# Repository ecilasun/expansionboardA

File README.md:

# expansionboardA

This repository contains KiCAD 7 project files for an expansion module built for QMTECH A7 200T core board.
Required libraries (models and symbols) are included with the project.

# Bill of materials

See expansionboardA.cv file for the list of components required for a fully populated board. Please note that some are optional (such as the USB controller chips) depending on your application.

# Default SoC, ROM image and samples

For hardware, visit https://github.com/ecilasun/tinysys. The project files require a recent version of Vivado suite to work.

For software, visit https://github.com/ecilasun/riscvtool and check the tinysys directory for the default ROM image and samples. The ROM image comes in two parts: the actual executable ROM and another one (fetch) that contains instruction sequences to inject on hardware/software interrupts. Samples demonstrate majority of the capabilities of the tinysys SoC itself.

# Device manual:
- Populating the board
    - USB-C power
    - Debug port
    - SD Card reader
    - HDMI port
    - A/D converter
    - USB-C client
    - USB-A host
    - Board carrier headers
    - Fan connection
    - Audio
    - QMTECH A7-200T core board
- Installing tinysys SoC bitware
- Compiling and running demo software on the board
    - Compiler toolchain installation
    - Hello, board!
- Operating system how-tos
    - List of syscalls
    - Memory layout
    - Operating principles
    - Debugging
- Device manuals:
    - Raw audio
    - OPL2 audio
    - GPU
    - DMA
    - A/D converter
    - Interrupt handling
    - Task system

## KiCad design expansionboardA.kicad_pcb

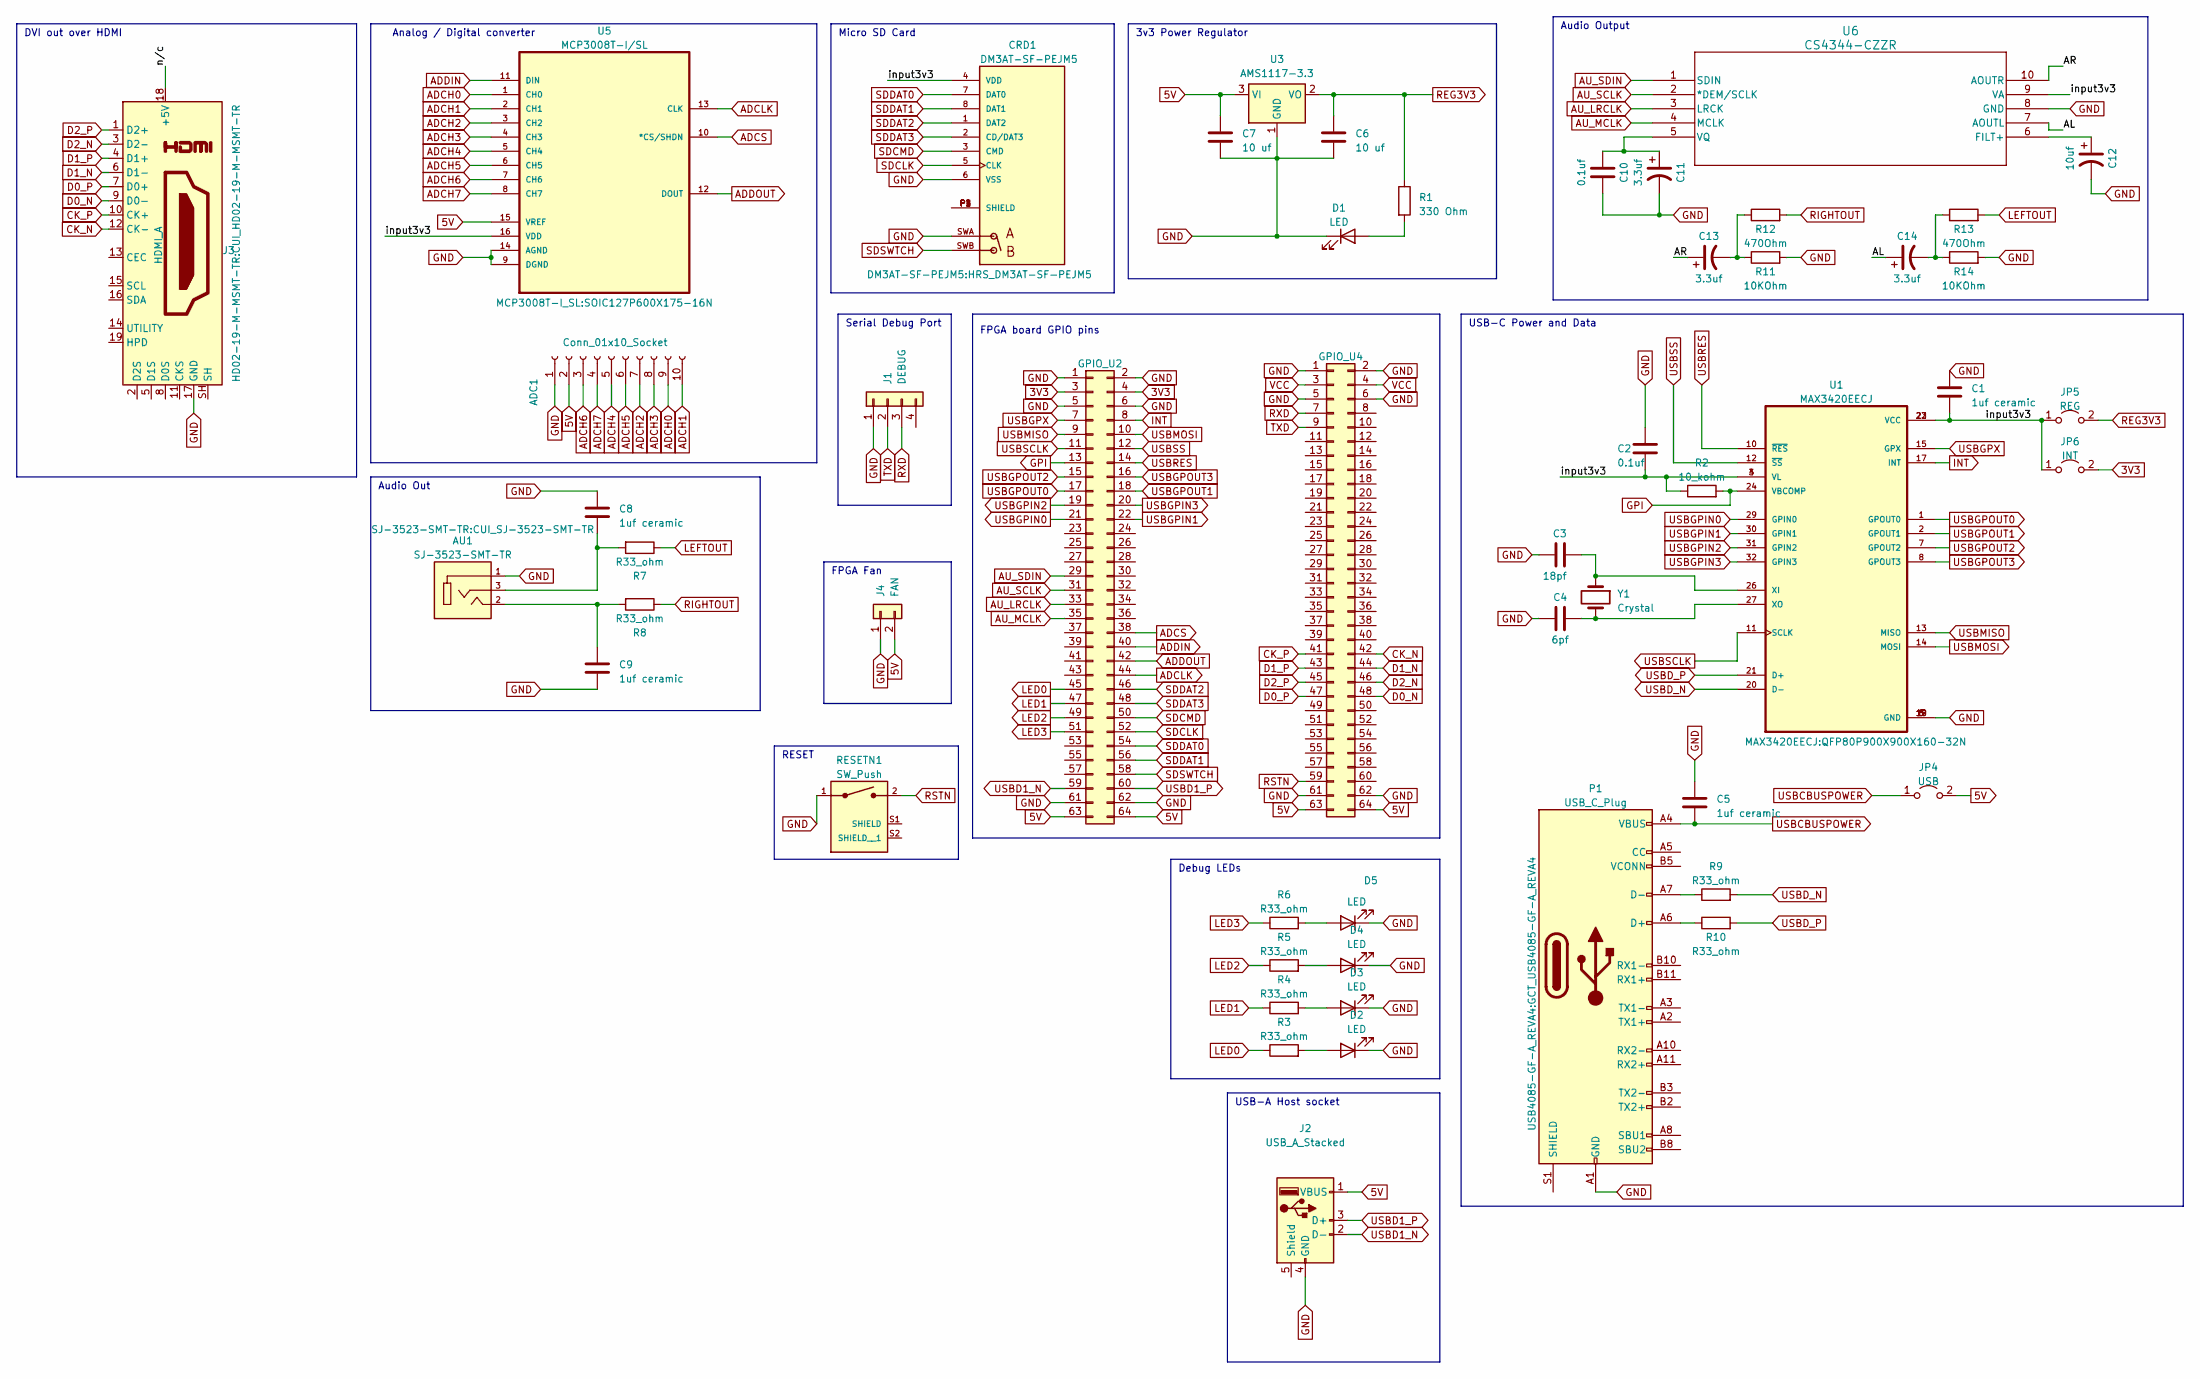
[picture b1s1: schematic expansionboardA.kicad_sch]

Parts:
ADC1: Conn_01x10_Socket; PinSocket_2x05_P2.54mm_Horizontal
AU1: SJ-3523-SMT-TR; CUI_SJ-3523-SMT-TR
C1, C5, C8, C9: 1uf ceramic; C_0603_1608Metric_Pad1.08x0.95mm_HandSolder
C2, C10: 0.1uf; C_0603_1608Metric_Pad1.08x0.95mm_HandSolder
C3: 18pf; C_0603_1608Metric_Pad1.08x0.95mm_HandSolder
C4: 6pf; C_0603_1608Metric_Pad1.08x0.95mm_HandSolder
C6, C7: 10 uf; C_0805_2012Metric_Pad1.18x1.45mm_HandSolder
C11, C13, C14: 3.3uf; CP_Radial_D10.0mm_P5.00mm
C12: 10uf; CP_Elec_6.3x5.9
CRD1: DM3AT-SF-PEJM5; HRS_DM3AT-SF-PEJM5
D1, D2, D3, D4, D5: LED; LED_1206_3216Metric_Pad1.42x1.75mm_HandSolder
J1: DEBUG; PinSocket_1x04_P2.54mm_Horizontal
J2: USB_A_Stacked; USB_A_Molex_67643_Horizontal
J3: HDMI_A; CUI_HD02-19-M-MSMT-TR
J4: FAN; PinHeader_1x02_P2.54mm_Vertical
JP4: USB; SolderJumper-2_P1.3mm_Open_Pad1.0x1.5mm
JP5: REG; SolderJumper-2_P1.3mm_Open_Pad1.0x1.5mm
JP6: INT; SolderJumper-2_P1.3mm_Open_Pad1.0x1.5mm
P1: USB_C_Plug; GCT_USB4085-GF-A_REVA4
R1: 330 Ohm; R_0603_1608Metric_Pad0.98x0.95mm_HandSolder
R2: 10_kohm; R_0603_1608Metric_Pad0.98x0.95mm_HandSolder
R3, R4, R5, R6, R7, R8, R9, R10: R33_ohm; R_0603_1608Metric_Pad0.98x0.95mm_HandSolder
R11, R14: 10KOhm; R_Axial_DIN0207_L6.3mm_D2.5mm_P7.62mm_Horizontal
R12, R13: 470Ohm; R_Axial_DIN0204_L3.6mm_D1.6mm_P5.08mm_Horizontal
RESETN1: SW_Push; SW_1-1825027-1; PARTREV G4
U1: MAX3420EECJ; QFP80P900X900X160-32N
U2: GPIO_U2; PinSocket_2x32_P2.54mm_Vertical
U3: AMS1117-3.3; SOT-89-3_Handsoldering
U4: GPIO_U4; PinSocket_2x32_P2.54mm_Vertical
U5: MCP3008T-I/SL; SOIC127P600X175-16N; MPN MCP3008T-I/SL
U6: CS4344-CZZR; CIR_3TSSOP-10
Y1: Crystal; Crystal_AT310_D3.0mm_L10.0mm_Horizontal

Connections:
3V3: JP6.2 (B), U2.3, U2.4
5V: ADC1.2, C7.1, J2.1 (VBUS), J4.2, JP4.2 (B), U2.63, U2.64, U3.3 (VI), U4.63, U4.64, U5.15 (VREF)
/AL: C14.1, U6.7 (AOUTL)
/AR: C13.1, U6.10 (AOUTR)
/input3v3: C1.2, C2.2, CRD1.4 (VDD), JP5.1 (A), JP6.1 (A), R2.1, U1.3 (VL), U1.4 (VL), U1.22 (VCC), U1.23 (VCC), U5.16 (VDD), U6.9 (VA)
/n/c: J3.18 (+5V)
ADCH0: ADC1.9, U5.1 (CH0)
ADCH1: ADC1.10, U5.2 (CH1)
ADCH2: ADC1.7, U5.3 (CH2)
ADCH3: ADC1.8, U5.4 (CH3)
ADCH4: ADC1.5, U5.5 (CH4)
ADCH5: ADC1.6, U5.6 (CH5)
ADCH6: ADC1.3, U5.7 (CH6)
ADCH7: ADC1.4, U5.8 (CH7)
ADCLK: U2.44, U5.13 (CLK)
ADCS: U2.38, U5.10 (*CS/SHDN)
ADDIN: U2.40, U5.11 (DIN)
ADDOUT: U2.42, U5.12 (DOUT)
AU_LRCLK: U2.33, U6.3 (LRCK)
AU_MCLK: U2.35, U6.4 (MCLK)
AU_SCLK: U2.31, U6.2 (*DEM/SCLK)
AU_SDIN: U2.29, U6.1 (SDIN)
CK_N: J3.12 (CK-), U4.42
CK_P: J3.10 (CK+), U4.41
D0_N: J3.9 (D0-), U4.48
D0_P: J3.7 (D0+), U4.47
D1_N: J3.6 (D1-), U4.44
D1_P: J3.4 (D1+), U4.43
D2_N: J3.3 (D2-), U4.46
D2_P: J3.1 (D2+), U4.45
GND: ADC1.1, AU1.1, C1.1, C2.1, C3.1, C4.1, C5.1, C6.2, C7.2, C8.1, C9.2, C10.2, C11.2, C12.2, CRD1.6 (VSS), CRD1.SWA, D1.1 (K), D2.1 (K), D3.1 (K), D4.1 (K), D5.1 (K), J1.1, J2.4 (GND), J3.17 (GND), J4.1, P1.A1 (GND), P1.A12 (GND), P1.B1 (GND), P1.B12 (GND), R11.2, R14.2, RESETN1.1, U1.5 (GND), U1.6 (GND), U1.18 (GND), U1.19 (GND), U2.1, U2.2, U2.5, U2.6, U2.61, U2.62, U3.1 (GND), U4.1, U4.2, U4.5, U4.6, U4.61, U4.62, U5.9 (DGND), U5.14 (AGND), U6.8 (GND)
GPI: R2.2, U1.24 (VBCOMP), U2.13
INT: U1.17 (INT), U2.8
LED0: R3.1, U2.45
LED1: R4.1, U2.47
LED2: R5.1, U2.49
LED3: R6.1, U2.51
LEFTOUT: R7.1, R13.2
unnamed: AU1.2, C9.1, R8.2
unnamed: AU1.3, C8.2, R7.2
unnamed: C13.2, R11.1, R12.1
unnamed: C14.2, R13.1, R14.1
unnamed: CRD1.P1 (SHIELD), CRD1.P2 (SHIELD), CRD1.P3 (SHIELD), CRD1.P4 (SHIELD)
unnamed: D1.2 (A), R1.2
unnamed: D2.2 (A), R3.2
unnamed: D3.2 (A), R4.2
unnamed: D4.2 (A), R5.2
unnamed: D5.2 (A), R6.2
unnamed: P1.A6 (D+), R10.1
unnamed: P1.A7 (D-), R9.1
unnamed: C3.2, U1.26 (XI), Y1.1
unnamed: C4.2, U1.27 (XO), Y1.2
unnamed: C12.1, U6.6 (FILT+)
unnamed: C10.1, C11.1, U6.5 (VQ)
REG3V3: C6.1, JP5.2 (B), R1.1, U3.2 (VO)
RIGHTOUT: R8.1, R12.2
RSTN: RESETN1.2, U4.59
RXD: J1.3, U4.7
SDCLK: CRD1.5 (CLK), U2.52
SDCMD: CRD1.3 (CMD), U2.50
SDDAT0: CRD1.7 (DAT0), U2.54
SDDAT1: CRD1.8 (DAT1), U2.56
SDDAT2: CRD1.1 (DAT2), U2.46
SDDAT3: CRD1.2 (CD/DAT3), U2.48
SDSWTCH: CRD1.SWB, U2.58
TXD: J1.2, U4.9
USBCBUSPOWER: C5.2, JP4.1 (A), P1.A4 (VBUS), P1.A9 (VBUS), P1.B4 (VBUS), P1.B9 (VBUS)
USBD1_N: J2.2 (D-), U2.59
USBD1_P: J2.3 (D+), U2.60
USBD_N: R9.2, U1.20 (D-)
USBD_P: R10.2, U1.21 (D+)
USBGPIN0: U1.29 (GPIN0), U2.21
USBGPIN1: U1.30 (GPIN1), U2.22
USBGPIN2: U1.31 (GPIN2), U2.19
USBGPIN3: U1.32 (GPIN3), U2.20
USBGPOUT0: U1.1 (GPOUT0), U2.17
USBGPOUT1: U1.2 (GPOUT1), U2.18
USBGPOUT2: U1.7 (GPOUT2), U2.15
USBGPOUT3: U1.8 (GPOUT3), U2.16
USBGPX: U1.15 (GPX), U2.7
USBMISO: U1.13 (MISO), U2.9
USBMOSI: U1.14 (MOSI), U2.10
USBRES: U1.10 (~RES), U2.14
USBSCLK: U1.11 (SCLK), U2.11
USBSS: U1.12 (~SS), U2.12
VCC: U4.3, U4.4

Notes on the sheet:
Serial Debug Port
Audio Output
USB-A Host socket
FPGA board GPIO pins
Micro SD Card
USB-C Power and Data
Debug LEDs
Audio Out
RESET
3v3 Power Regulator
DVI out over HDMI
FPGA Fan
Analog / Digital converter

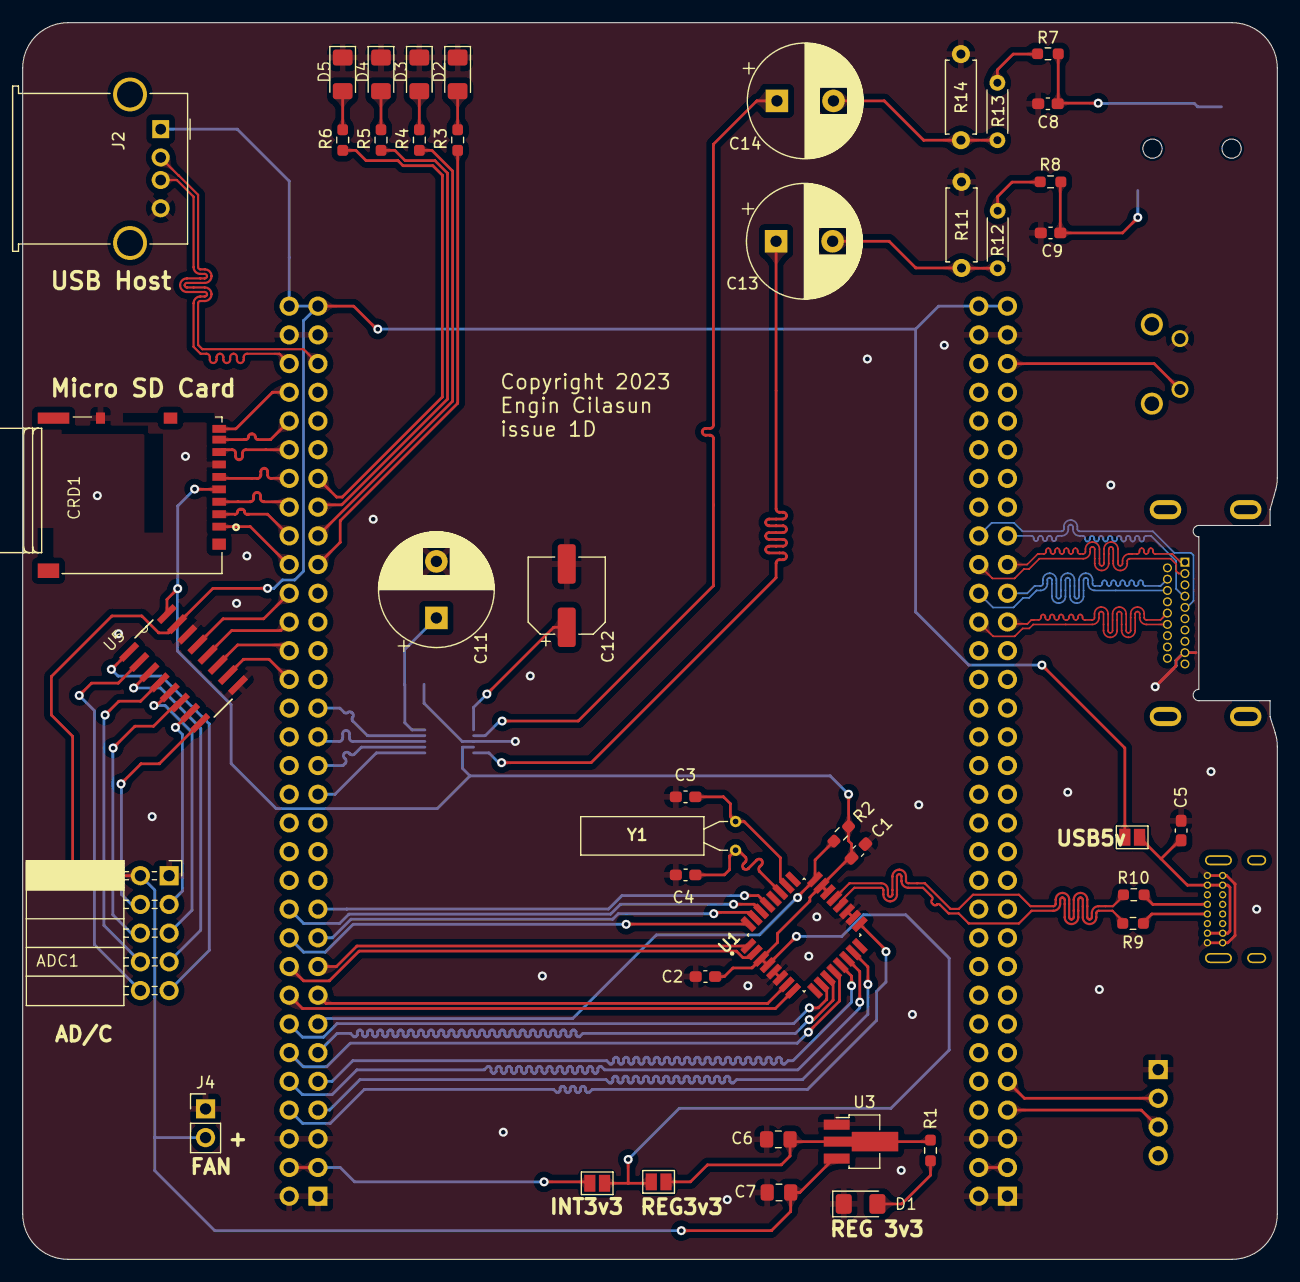
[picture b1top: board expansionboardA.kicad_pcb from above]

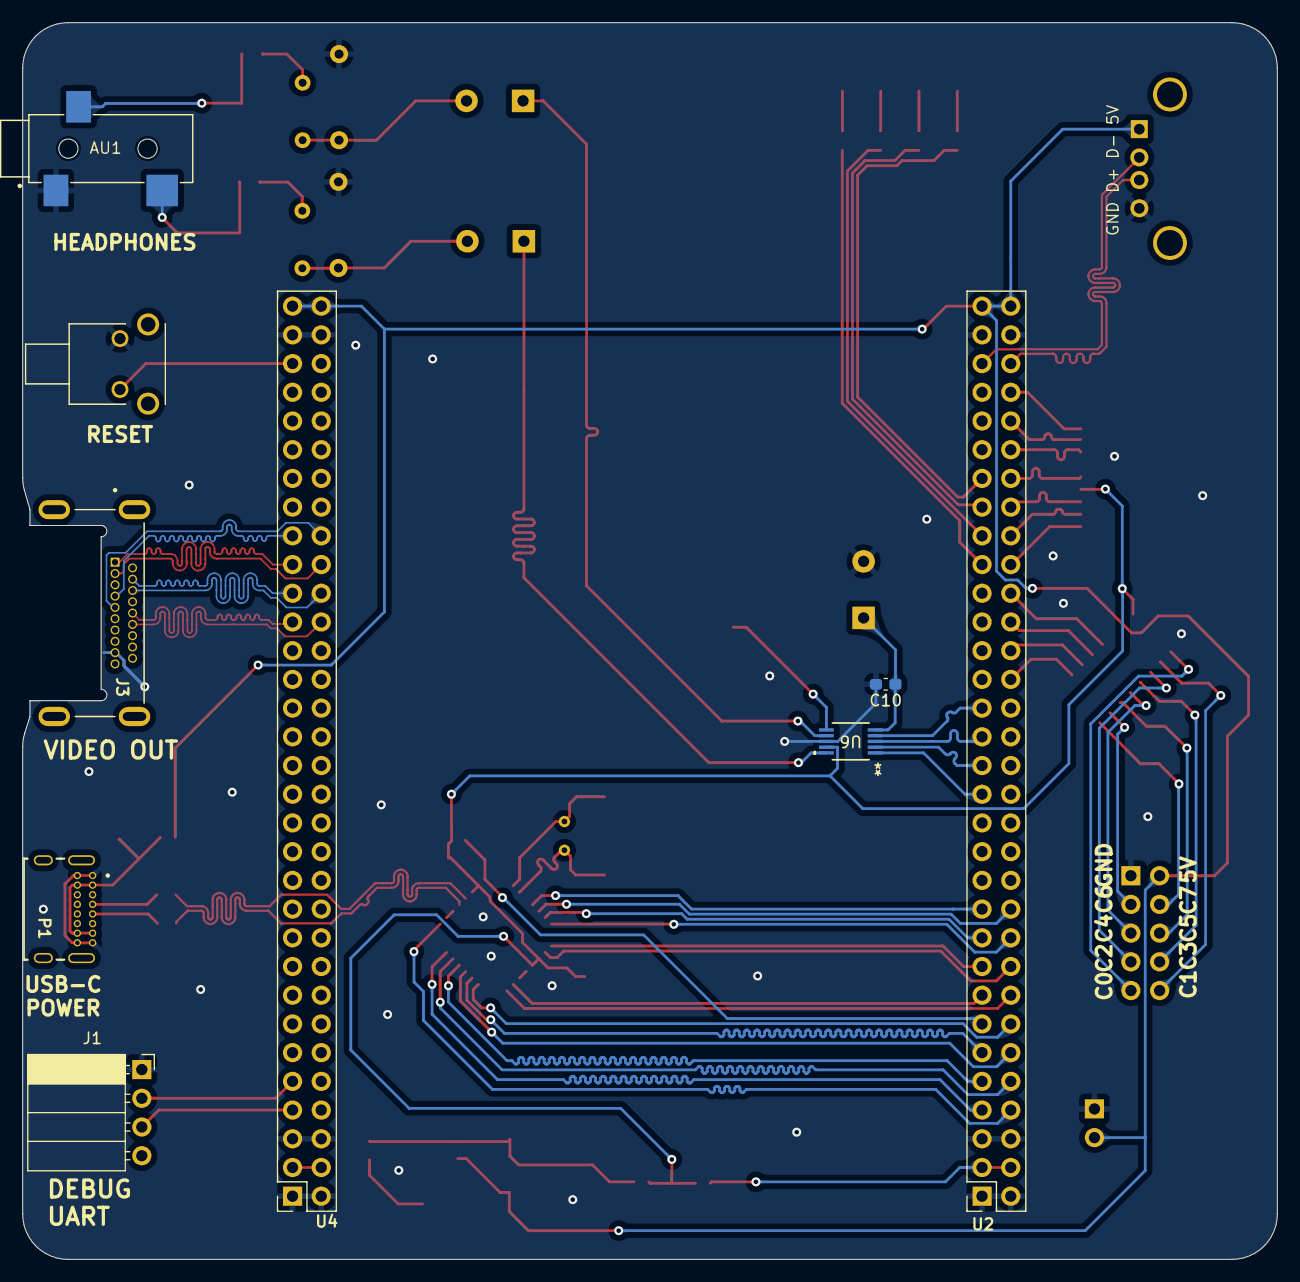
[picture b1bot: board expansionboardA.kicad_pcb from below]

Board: 2 copper layers, 111.0 x 109.4 mm, 52 parts (9 on the bottom side), 85 nets.

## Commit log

2023-03-30 Initial submit
2023-03-30 Small layout edits
2023-03-31 Board updated
2023-03-31 Updated schematic with correct parts Built gerber files
2023-03-31 Copied bill of materials CVS file
2023-03-31 Updated board with USB A host connector
2023-03-31 Updated bill of materials
2023-03-31 Default setup
2023-04-07 Exported board step file
2023-04-11 Updated board
2023-04-17 Updatre board version
2023-04-17 Updated board files
2023-04-19 Updated board to fix some issues
2023-04-23 Updated to new board version
2023-04-24 Updated board image
2023-04-24 Rebuilt board
2023-04-28 Board updates
2023-04-30 Adding USB host chip
2023-04-30 Mechanical bits
2023-05-06 Fixed some errors on the board
2023-05-08 Cleaned up board layout
2023-05-08 updated render
2023-05-08 Updated board traces
2023-05-08 Updat4ed some routing
2023-05-09 Board changes
2023-05-28 Smoothed traces
2023-05-29 Some modifications for mount holes and expansion port Also added optional pullup resistors
2023-06-26 Updated board file with new power regulator
2023-06-26 Updated renders
2023-06-28 mods

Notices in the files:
expansionboardA.kicad_pcb:
Copyright 2023
